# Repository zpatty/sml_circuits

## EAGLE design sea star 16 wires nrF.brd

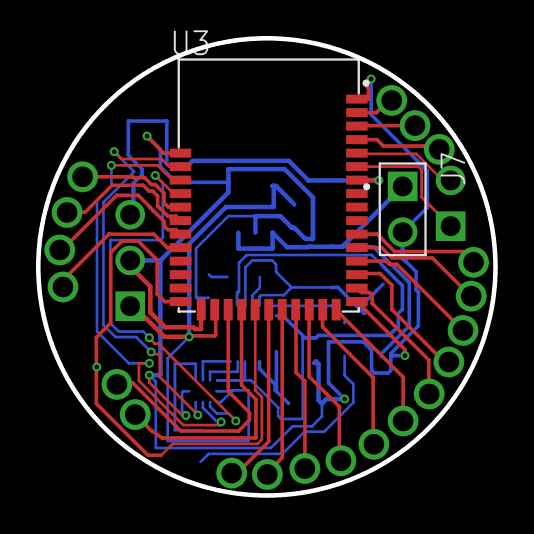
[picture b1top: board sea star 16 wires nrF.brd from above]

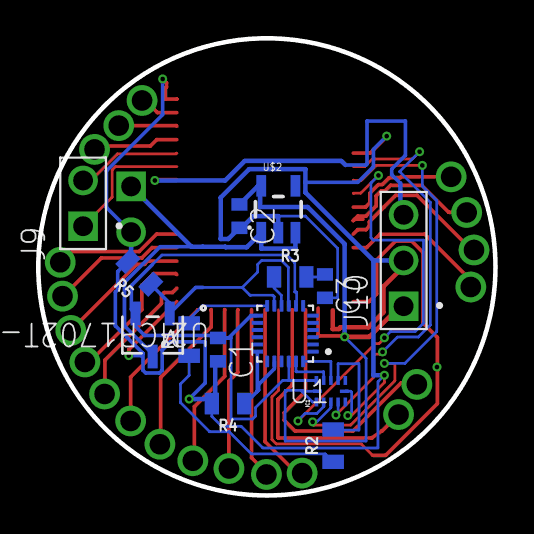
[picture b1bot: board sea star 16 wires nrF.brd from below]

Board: 2 copper layers, 25.4 x 25.4 mm, 16 parts (14 on the bottom side), 20 nets.

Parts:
C1, C2, C3: C0402
IC1: NTS0104GU12; QFN40P170X200X50-12N
J7, J9: 61300211121
J10: 61300311121
R1, R2, R3, R4, R5: 0805
U1: ICM-20948; QFN40P300X300X105-24N
U2: MCP1702T-1802E/CB; SOT-23A_MC
U3: BL652-SA-01; XCVR_BL652-SA-01
U$2: SPX3819M5_3_3; SOT23-5

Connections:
+1.8V: C1.1, IC1.11, U1.8, U1.13, U1.22, U2.2
+3V: C2.1, IC1.1, IC1.12, J10.1, U3.26, U$2.5
GND: C1.2, C2.2, C3.2, IC1.6, J7.2, J10.2, R4.2, R5.2, U3.1, U3.16, U3.27, U3.39, U$2.2
GND1: R5.1, U1.9, U1.11, U2.1
GND2: R4.1, U1.18, U1.20
INT_A: IC1.4, U3.38
INT_B: R1.1, R2.1
unnamed: R3.1, U1.10
unnamed: C3.1, R3.2
unnamed: R1.2, U1.12
unnamed: IC1.8, R2.2
unnamed: U3.23, U3.28
RESET: J10.3, U3.7
SCL_A: IC1.2, U3.36
SCL_B: IC1.10, U1.23
SDA_A: IC1.3, U3.37
SDA_B: IC1.9, U1.24
SWDCLK: J9.1, U3.6
SWDIO: J9.2, U3.5
VBAT_1: J7.1, U2.3, U$2.1, U$2.3

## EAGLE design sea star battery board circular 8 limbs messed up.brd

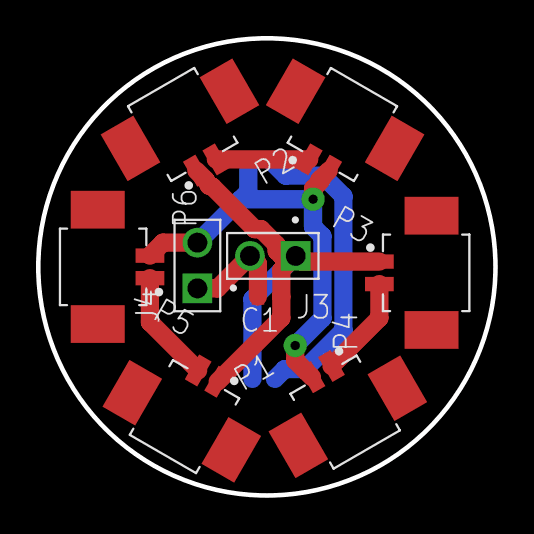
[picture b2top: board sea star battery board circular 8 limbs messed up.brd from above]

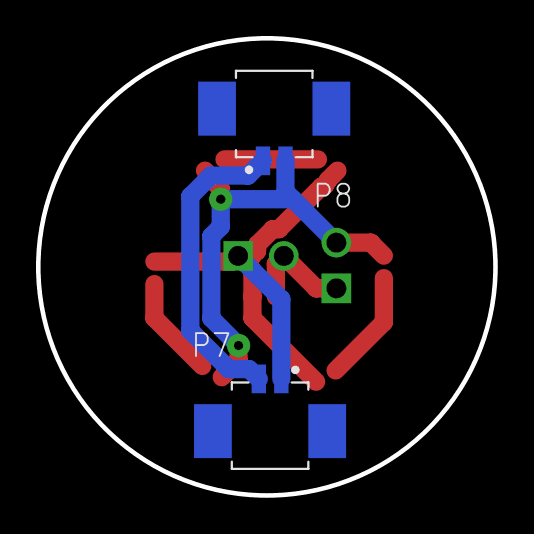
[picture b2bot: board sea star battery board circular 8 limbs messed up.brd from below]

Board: 2 copper layers, 25.4 x 25.4 mm, 11 parts (2 on the bottom side), 7 nets.

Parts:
C1: C0402
J3, J4: 61300211121
P1, P2, P3, P4, P5, P6, P7, P8: 0532610271; MOLEX_0532610271

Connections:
GND: C1.2, J3.2, J4.1
unnamed: P2.2, P3.1
unnamed: J4.2, P1.2, P3.2, P6.2, P8.2
unnamed: P5.2, P6.1
unnamed: P1.1, P4.2
unnamed: P7.2, P8.1
PWR: C1.1, J3.1, P2.1, P4.1, P5.1, P7.1

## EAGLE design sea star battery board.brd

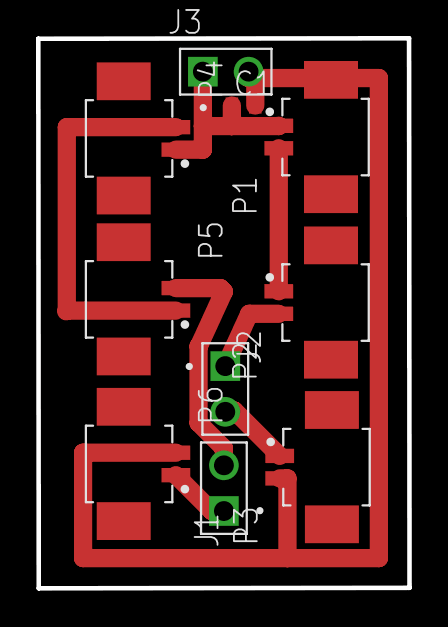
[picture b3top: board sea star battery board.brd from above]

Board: 2 copper layers, 20.6 x 30.6 mm, 10 parts (0 on the bottom side), 8 nets.

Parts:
C1: C0402
J1, J2, J3: 61300211121
P1, P2, P3, P4, P5, P6: 0532610271; MOLEX_0532610271

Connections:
GND: C1.2, J3.2, P3.2, P6.2
unnamed: J2.2, P3.1
unnamed: J2.1, P2.2
unnamed: C1.1, J3.1, P1.1, P4.1
unnamed: P1.2, P2.1
unnamed: J1.1, P6.1
unnamed: P4.2, P5.1
unnamed: J1.2, P5.2

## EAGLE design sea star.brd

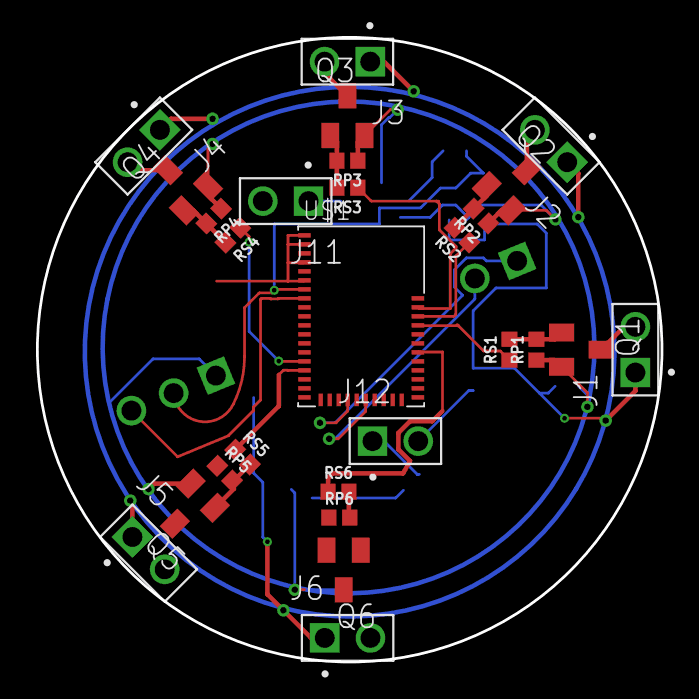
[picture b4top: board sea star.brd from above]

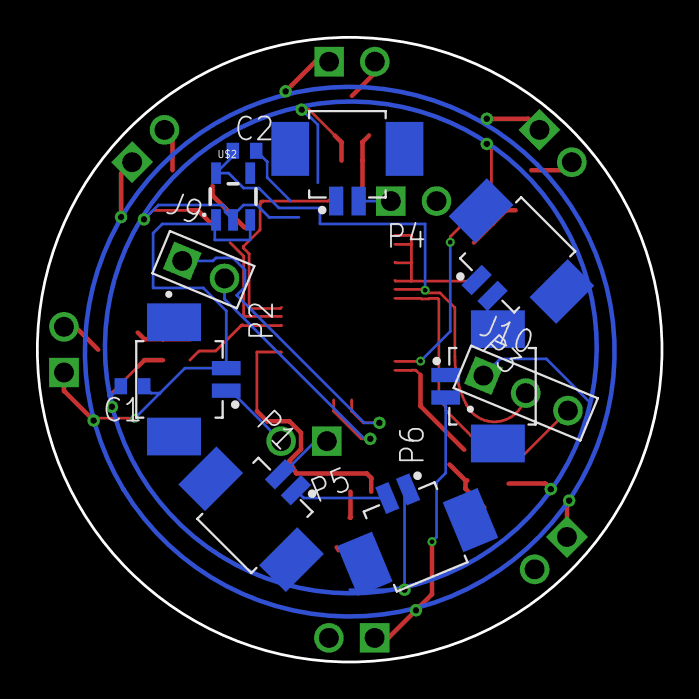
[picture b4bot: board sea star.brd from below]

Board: 2 copper layers, 34.7 x 34.7 mm, 38 parts (11 on the bottom side), 31 nets.

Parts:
C1, C2: C0402
J1, J2, J3, J4, J5, J6, J9, J11, J12: 61300211121
J10: 61300311121
P1, P2, P3, P4, P5, P6: 0532610271; MOLEX_0532610271
Q1, Q2, Q3, Q4, Q5, Q6: SOT23
RP1, RP2, RP3, RP4, RP5, RP6: 0402
RS1, RS2, RS3, RS4, RS5, RS6: 0402
U$1: RFD77101
U$2: SPX3819M5_3_3; SOT23-5

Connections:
+3V: C2.1, J10.2, U$1.7, U$2.5
GND: C1.2, C2.2, J10.1, P4.1, P5.1, Q1.2, Q2.2, Q3.2, Q4.2, Q5.2, Q6.2, RP1.1, RP2.1, RP3.1, RP4.1, RP5.1, RP6.1, U$1.1, U$1.2, U$1.4, U$1.6, U$1.19, U$1.30, U$2.2
GPIO0: J9.2, U$1.25
GPIO1: J9.1, U$1.23
unnamed: Q1.1, RP1.2, RS1.2
unnamed: Q2.1, RP2.2, RS2.2
unnamed: Q3.1, RP3.2, RS3.2
unnamed: Q4.1, RP4.2, RS4.2
unnamed: Q5.1, RP5.2, RS5.2
unnamed: Q6.1, RP6.2, RS6.2
unnamed: P1.1, P5.2
unnamed: J12.2, P2.1
unnamed: J11.1, P4.2
unnamed: P3.2, P6.1
unnamed: J11.2, P3.1
unnamed: J12.1, P1.2
RESET: J10.3, U$1.8
SMA1_PWR: J1.2, Q1.3
SMA1_SIG: RS1.1, U$1.38
SMA2_PWR: J2.2, Q2.3
SMA2_SIG: RS2.1, U$1.39
SMA3_PWR: J3.2, Q3.3
SMA3_SIG: RS3.1, U$1.40
SMA4_PWR: J4.2, Q4.3
SMA4_SIG: RS4.1, U$1.15
SMA5_PWR: J5.2, Q5.3
SMA5_SIG: RS5.1, U$1.16
SMA6_PWR: J6.2, Q6.3
SMA6_SIG: RS6.1, U$1.35
VBAT_1: C1.1, J1.1, J2.1, J3.1, J4.1, P2.2, U$2.1, U$2.3
VBAT_2: J5.1, J6.1, P6.2

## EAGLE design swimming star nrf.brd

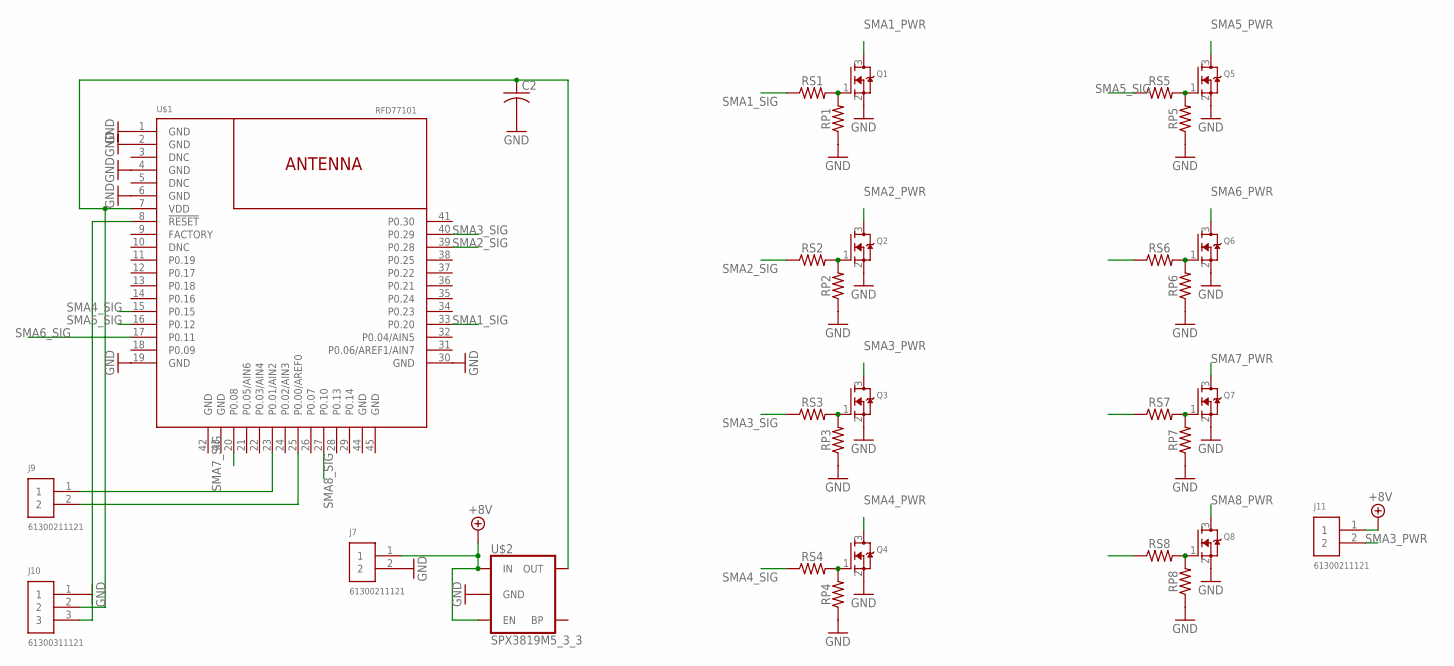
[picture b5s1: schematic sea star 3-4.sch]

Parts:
C2: C-USC0402; C0402
J7, J9, J11: 61300211121
J10: 61300311121
Q1, Q2, Q3, Q4, Q5, Q6, Q7, Q8: MOSFET-NREFLOW; SOT23
RP1, RP2, RP3, RP4, RP5, RP6, RP7, RP8: 0402
RS1, RS2, RS3, RS4, RS5, RS6, RS7, RS8: 0402
U$1: RFD77101
U$2: SPX3819M5_3_3; SOT23-5

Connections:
+3V: C2.1, J10.2, U$1.7 (VDD), U$2.5 (OUT); also elsewhere on the board
GND: C2.2, J7.2, J10.1, Q1.2 (S), Q2.2 (S), Q3.2 (S), Q4.2 (S), Q5.2 (S), Q6.2 (S), Q7.2 (S), Q8.2 (S), RP1.1, RP2.1, RP3.1, RP4.1, RP5.1, RP6.1, RP7.1, RP8.1, U$1.1 (GND), U$1.2 (GND), U$1.4 (GND), U$1.6 (GND), U$1.19 (GND), U$1.30 (GND), U$2.2 (GND); also elsewhere on the board
GPIO0: J9.2, U$1.25 (P0.00/AREF0); also elsewhere on the board
GPIO1: J9.1, U$1.23 (P0.01/AIN2); also elsewhere on the board
unnamed: Q1.1 (G), RP1.2, RS1.2
unnamed: Q2.1 (G), RP2.2, RS2.2
unnamed: Q3.1 (G), RP3.2, RS3.2
unnamed: Q4.1 (G), RP4.2, RS4.2
unnamed: Q5.1 (G), RP5.2, RS5.2
unnamed: Q6.1 (G), RP6.2, RS6.2
unnamed: Q7.1 (G), RP7.2, RS7.2
unnamed: Q8.1 (G), RP8.2, RS8.2
RESET: J10.3, U$1.8 (!RESET!); also elsewhere on the board
SMA1_PWR: Q1.3 (D)
SMA1_SIG: RS1.1, U$1.33 (P0.20); also elsewhere on the board
SMA2_PWR: Q2.3 (D)
SMA2_SIG: RS2.1, U$1.39 (P0.28); also elsewhere on the board
SMA3_PWR: J11.2, Q3.3 (D)
SMA3_SIG: RS3.1, U$1.40 (P0.29); also elsewhere on the board
SMA4_PWR: Q4.3 (D)
SMA4_SIG: RS4.1, U$1.15 (P0.15); also elsewhere on the board
SMA5_PWR: Q5.3 (D)
SMA5_SIG: RS5.1, U$1.16 (P0.12); also elsewhere on the board
SMA6_PWR: Q6.3 (D)
SMA6_SIG: RS6.1, U$1.17 (P0.11); also elsewhere on the board
SMA7_PWR: Q7.3 (D)
SMA7_SIG: RS7.1, U$1.20 (P0.08); also elsewhere on the board
SMA8_PWR: Q8.3 (D)
SMA8_SIG: RS8.1, U$1.27 (P0.10); also elsewhere on the board
VBAT_1: J7.1, J11.1, U$2.1 (IN), U$2.3 (EN)

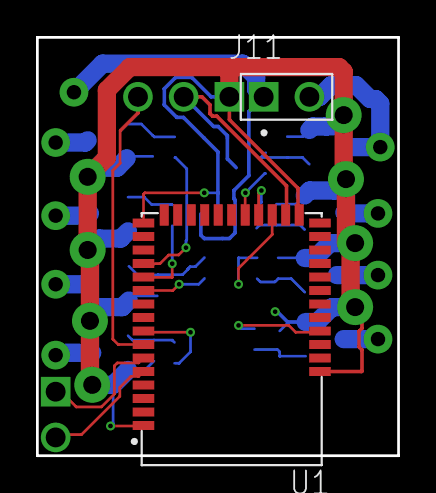
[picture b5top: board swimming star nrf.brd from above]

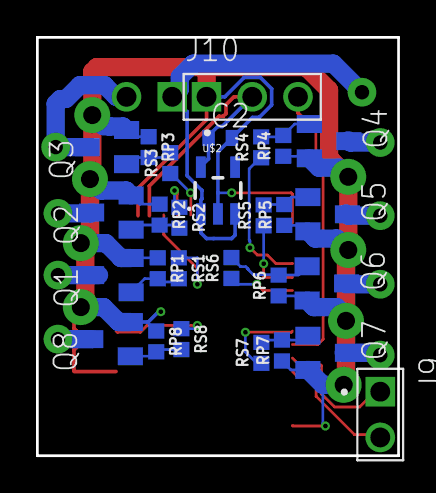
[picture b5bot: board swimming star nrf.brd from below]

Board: 2 copper layers, 20.1 x 23.2 mm, 30 parts (28 on the bottom side), 23 nets.

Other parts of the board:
U1: BL652-SA-01; XCVR_BL652-SA-01

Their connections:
+3V: U1.26; also elsewhere on the board
GND: U1.1, U1.16, U1.27, U1.39; also elsewhere on the board
GPIO0: U1.5; also elsewhere on the board
GPIO1: U1.6; also elsewhere on the board
RESET: U1.7; also elsewhere on the board
SMA1_SIG: U1.25; also elsewhere on the board
SMA2_SIG: U1.24; also elsewhere on the board
SMA3_SIG: U1.23; also elsewhere on the board
SMA4_SIG: U1.13; also elsewhere on the board
SMA5_SIG: U1.12; also elsewhere on the board
SMA6_SIG: U1.11; also elsewhere on the board
SMA7_SIG: U1.8; also elsewhere on the board
SMA8_SIG: U1.36; also elsewhere on the board

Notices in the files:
parts and their libraries:
SparkFun-IC-Power: Licensing: Creative Commons ShareAlike 4.0 International - https://creativecommons.org/licenses/by-sa/4.0
COPYRIGHT: Copyright (C) 2018 Accelerated Designs. All rights reserved
RFDigital: © 2015 RF Digital Corporation
